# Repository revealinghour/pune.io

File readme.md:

https://www.sparkfun.com/tutorials/393
https://www.kickstarter.com/projects/acrobotic/the-smart-citizen-kit-crowdsourced-environmental-m

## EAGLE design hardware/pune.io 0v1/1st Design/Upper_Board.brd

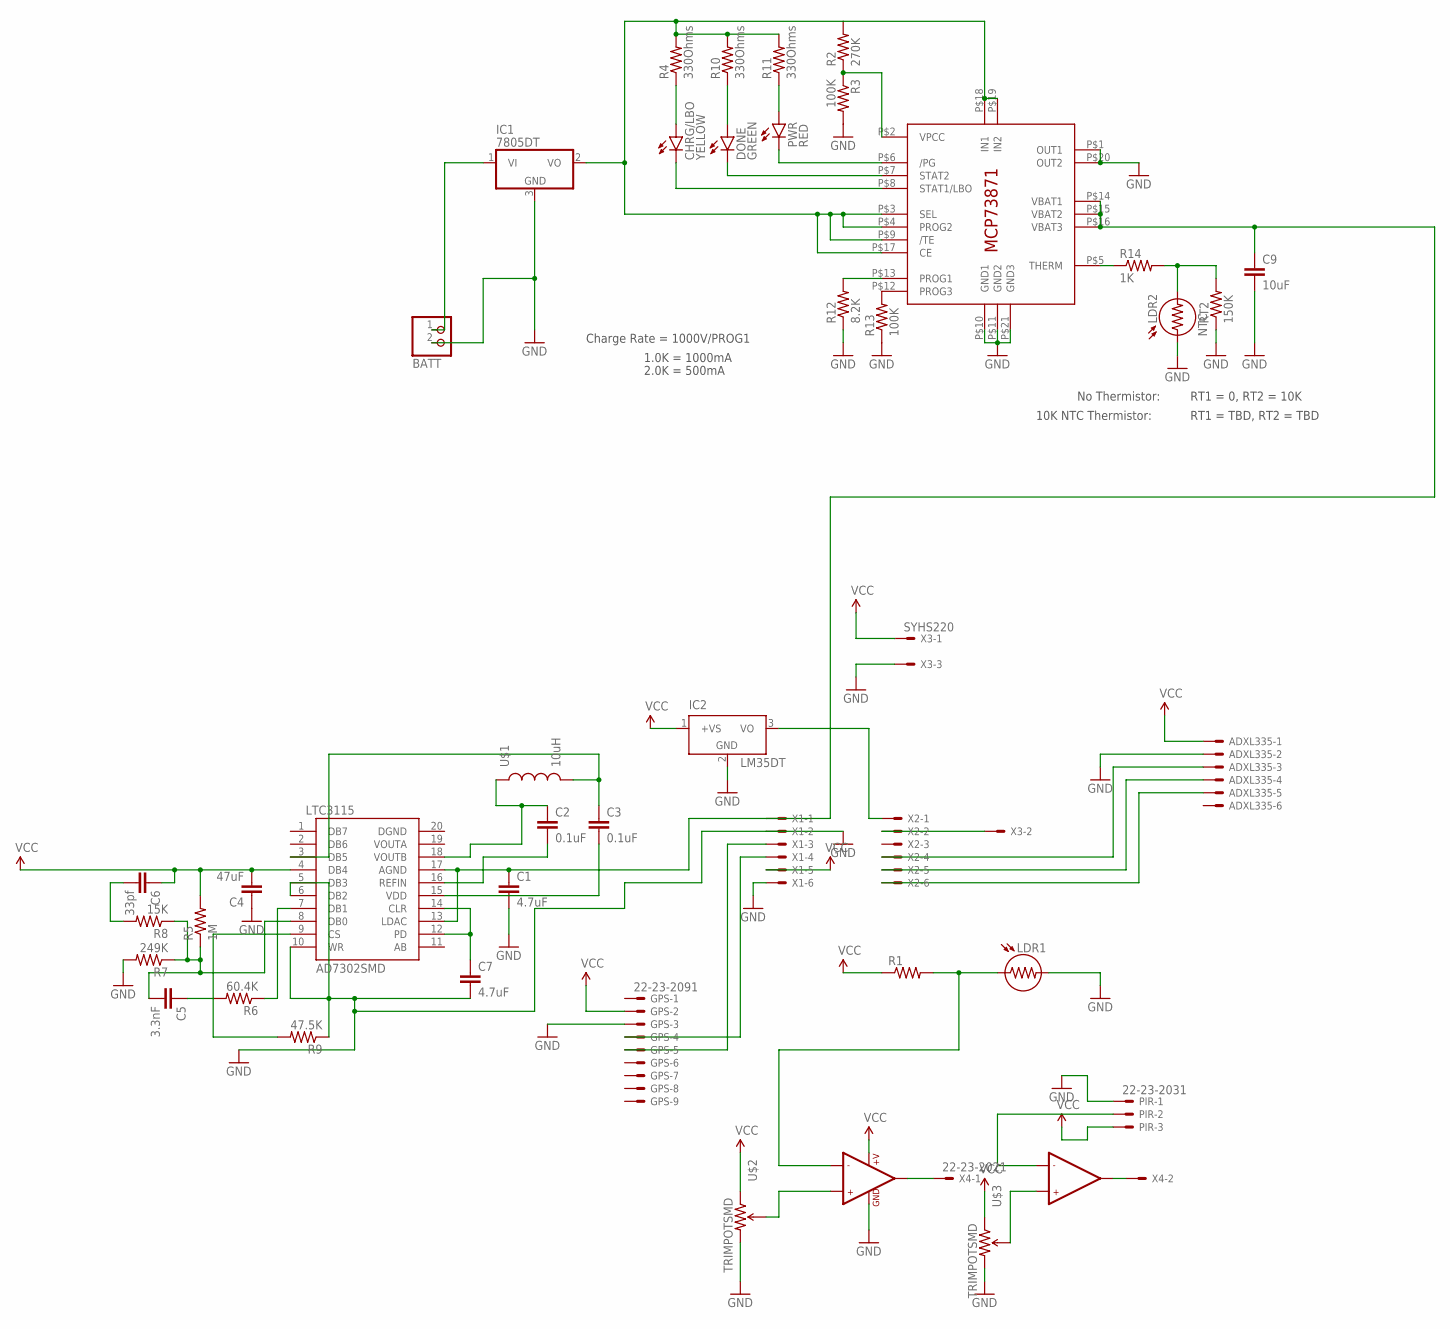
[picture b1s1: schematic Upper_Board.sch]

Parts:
ADXL335: 22-23-2061
BATT: JST_2PIN-SMT-RA; JST-PH-2-SMT-RA
C1, C7: 4.7uF; 0603-CAP
C2, C3: 0.1uF; 0603-CAP
C4: 47uF; 0603-CAP
C5: 3.3nF; 0603-CAP
C6: 33pf; 0603-CAP
C9: 10uF; 0603-CAP
CHRG/LBO: YELLOW; LED-1206
DONE: GREEN; LED-1206
GPS: 22-23-2091
IC1: 7805DT; TO252
IC2: LM35DT; TO220V
IC4: MCP73871; QFN20_4MM
LDR1: LDR5MM; LDR338-54C
LDR2: NTC; LDR338-54C
LTC3115: AD7302SMD; TSSOP20
PIR: 22-23-2031
PWR: RED; LED-1206
R1: RESISTOR1206; 1206
R2: 270K; 1206
R3, R13: 100K; 1206
R4, R10, R11: 330Ohms; 1206
R5: 1M; 1206
R6: 60.4K; 1206
R7: 249K; 1206
R8: 15K; 1206
R9: 47.5K; 1206
R12: 8.2K; 1206
R14: 1K; 1206
RT2: 150K; 1206
U$1: 10uH; INDUCTOR-1206
U$2, U$3: TRIMPOTSMD; TRIMPOT-3MM
U$4: LMV358; SO08
X1, X2: 22-23-2061
X3: SYHS220; 22-23-2031
X4: 22-23-2021

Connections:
BATT: C1.1, C9.1, IC4.P$14 (VBAT1), IC4.P$15 (VBAT2), IC4.P$16 (VBAT3), LTC3115.13 (LDAC), LTC3115.17 (AGND), X1.1
GND: ADXL335.2, BATT.2 (1), C1.2, C4.1, C7.2, C9.2, GPS.3, IC1.3 (GND), IC2.2 (GND), IC4.P$1 (OUT1), IC4.P$10 (GND1), IC4.P$11 (GND2), IC4.P$20 (OUT2), IC4.P$21 (GND3), LDR1.2, LDR2.1, LTC3115.5 (DB3), LTC3115.6 (DB2), LTC3115.10 (WR), PIR.1, R3.2, R7.2, R9.1, R12.1, R13.1, RT2.1, U$2.3 (CW), U$3.3 (CW), U$4.4 (GND), X1.2, X1.6, X3.3
unnamed: LDR1.1, R1.2, U$4.2 (-IN1)
unnamed: IC2.3 (VO), X2.1
unnamed: U$4.1 (OUT1), X4.1
unnamed: U$4.7 (OUT2), X4.2
unnamed: U$2.2 (WIPER), U$4.3 (+IN1)
unnamed: U$3.2 (WIPER), U$4.5 (+IN2)
unnamed: X2.2, X3.2
unnamed: IC4.P$2 (VPCC), R2.1, R3.1
unnamed: ADXL335.3, X2.4
unnamed: PIR.2, U$4.6 (-IN2)
unnamed: ADXL335.4, X2.5
unnamed: ADXL335.5, X2.6
unnamed: IC4.P$6 (/PG), PWR.C
unnamed: DONE.C, IC4.P$7 (STAT2)
unnamed: CHRG/LBO.C, IC4.P$8 (STAT1/LBO)
unnamed: C2.2, LTC3115.16 (REFIN)
unnamed: C2.1, LTC3115.18 (VOUTB), U$1.P$1 (1)
unnamed: C3.1, LTC3115.3 (DB5), U$1.P$2 (2)
unnamed: C3.2, LTC3115.15 (VDD)
unnamed: CHRG/LBO.A, R4.1
unnamed: LTC3115.7 (DB1), R6.1
unnamed: C5.1, R6.2
unnamed: C5.2, LTC3115.8 (DB0), R5.1, R7.1, R8.1
unnamed: DONE.A, R10.1
unnamed: C6.2, R8.2
unnamed: PWR.A, R11.1
unnamed: C7.1, LTC3115.12 (PD), LTC3115.14 (CLR)
unnamed: IC4.P$12 (PROG3), R13.2
unnamed: IC4.P$13 (PROG1), R12.2
unnamed: LTC3115.9 (CS), R9.2
unnamed: IC4.P$5 (THERM), R14.1
unnamed: LDR2.2, R14.2, RT2.2
unnamed: IC1.2 (VO), IC4.P$3 (SEL), IC4.P$4 (PROG2), IC4.P$9 (/TE), IC4.P$17 (CE), IC4.P$18 (IN1), IC4.P$19 (IN2), R2.2, R4.2, R10.2, R11.2
unnamed: GPS.4, X1.4
unnamed: GPS.5, X1.3
unnamed: BATT.1 (2), IC1.1 (VI)
VCC: ADXL335.1, C4.2, C6.1, GPS.2, IC2.1 (+VS), LTC3115.4 (DB4), PIR.3, R1.1, R5.2, U$2.1 (CCW), U$3.1 (CCW), U$4.8 (+V), X1.5, X3.1

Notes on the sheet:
Charge Rate = 1000V/PROG1
1.0K = 1000mA
2.0K = 500mA
No Thermistor:
10K NTC Thermistor:
RT1 = 0, RT2 = 10K
RT1 = TBD, RT2 = TBD

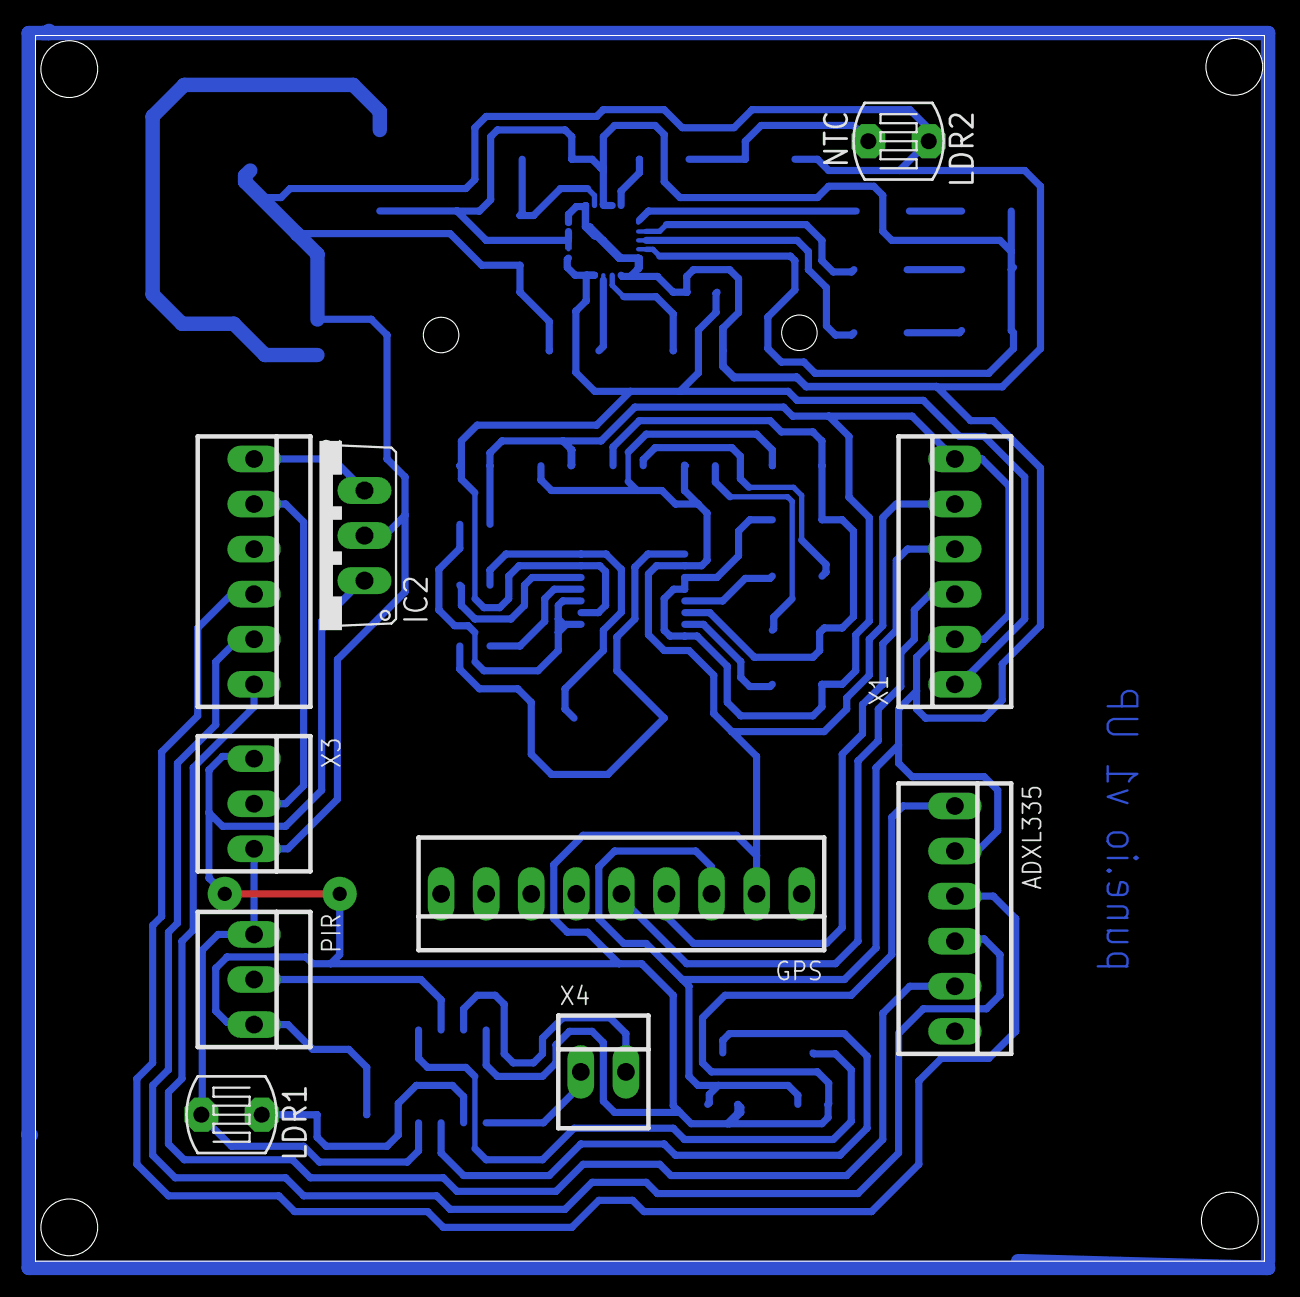
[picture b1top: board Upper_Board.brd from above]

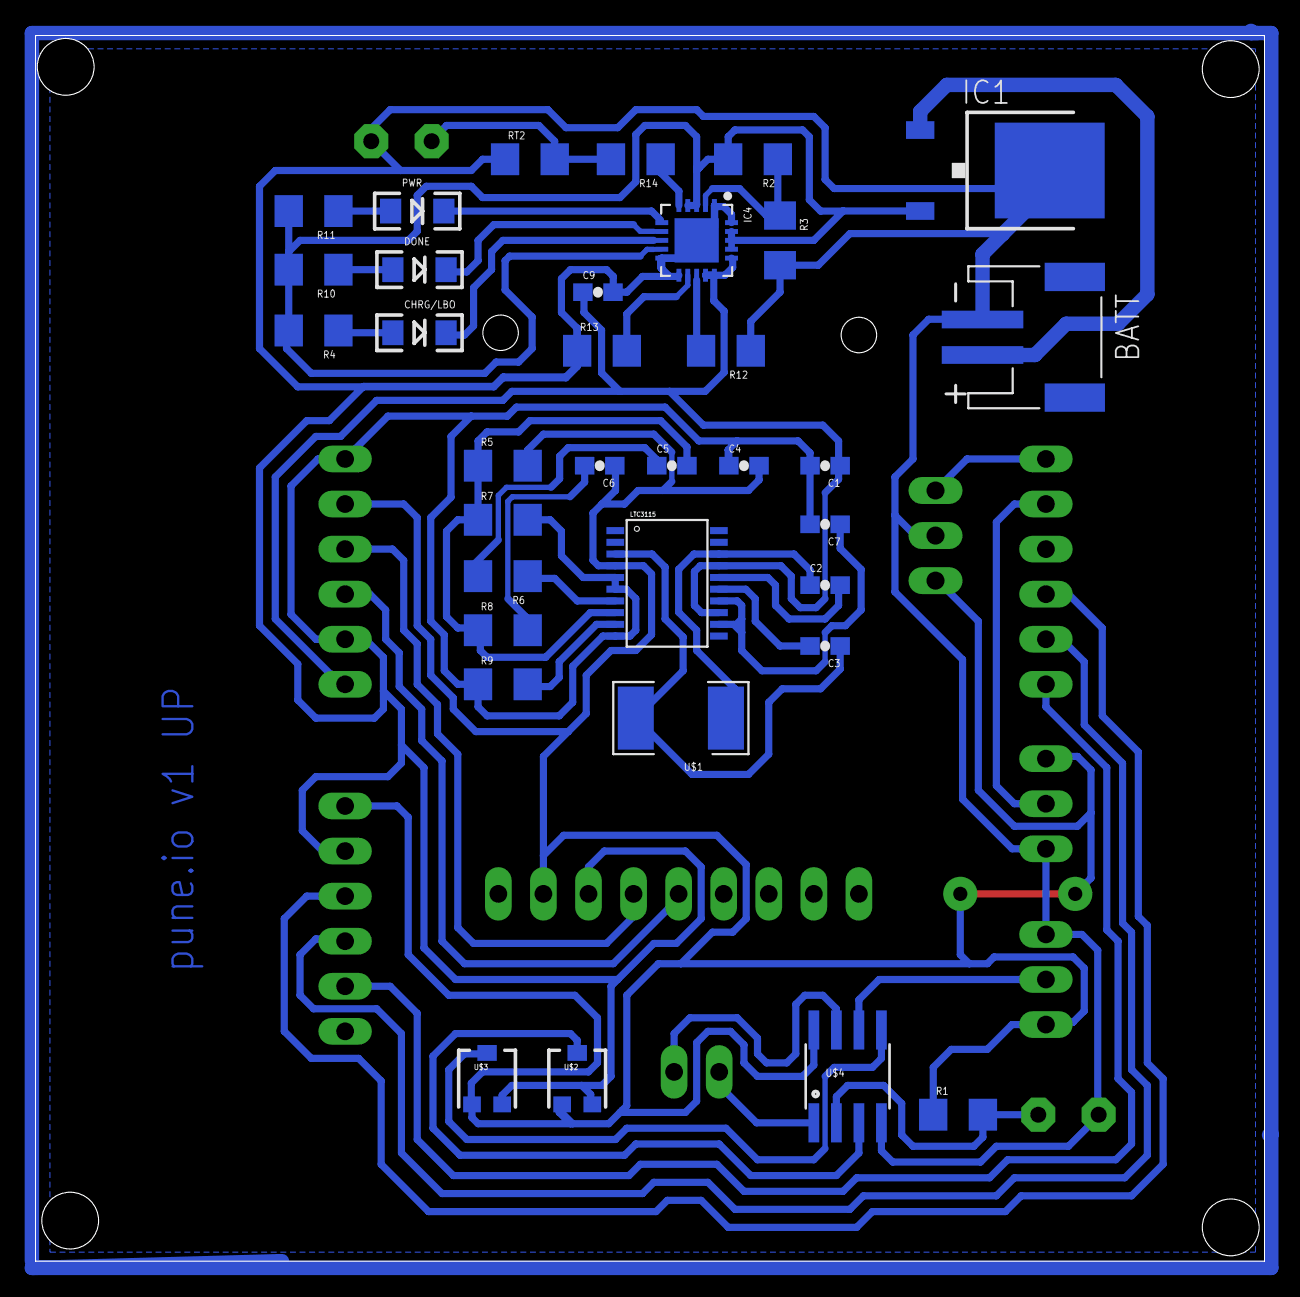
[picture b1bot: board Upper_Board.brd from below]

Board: 2 copper layers, 69.3 x 69.1 mm, 44 parts (34 on the bottom side), 39 nets.

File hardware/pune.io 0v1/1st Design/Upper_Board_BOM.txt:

Partlist exported from /home/tanmayee/eagle/Rev/Upper_Board.sch at 20/02/15 6:37 PM

Part     Value      Device          Package         Description                                 MF    MPN        OC_FARNELL OC_NEWARK PROD_ID   VALUE 
ADXL335             22-23-2061      22-23-2061      .100" (2.54mm) Center Header - 6 Pin        MOLEX 22-23-2061 1462922    27C1933                   
BATT                JST_2PIN-SMT-RA JST-PH-2-SMT-RA JST 2-Pin Connectors of various flavors                                                           
C1       4.7uF      CAP0603-CAP     0603-CAP        Capacitor                                                                                         
C2       0.1uF      CAP0603-CAP     0603-CAP        Capacitor                                                                                         
C3       0.1uF      CAP0603-CAP     0603-CAP        Capacitor                                                                                         
C4       47uF       CAP0603-CAP     0603-CAP        Capacitor                                                                                         
C5       3.3nF      CAP0603-CAP     0603-CAP        Capacitor                                                                                         
C6       33pf       CAP0603-CAP     0603-CAP        Capacitor                                                                                         
C7       4.7uF      CAP0603-CAP     0603-CAP        Capacitor                                                                                         
C9       10uF       CAP0603-CAP     0603-CAP        Capacitor                                                                                         
CHRG/LBO YELLOW     LED-YELLOWLARGE LED-1206        Yellow SMD LEDs                                                                   DIO-00820 YELLOW
DONE     GREEN      LED-GREENLARGE  LED-1206        Various green LEDs                                                                DIO-00862 GREEN 
GPS      22-23-2091 22-23-2091      22-23-2091      .100" (2.54mm) Center Header - 9 Pin        MOLEX 22-23-2091 1756827    56H0450                   
IC1      7805DT     7805DT          TO252           Positive VOLTAGE REGULATOR                                                                        
IC2      LM35DT     LM35DT          TO220V          Single-Supply Centigrade Temperature Sensor                                                       
IC4      MCP73871   MCP73871        QFN20_4MM                                                                                                         
LDR1                LDR5MM          LDR338-54C                                                                                                        
LDR2     NTC        LDR5MM          LDR338-54C                                                                                                        
LTC3115  AD7302SMD  AD7302SMD       TSSOP20         8-bit parallel input 2-output DAC                                                                 
PIR      22-23-2031 22-23-2031      22-23-2031      .100" (2.54mm) Center Header - 3 Pin        MOLEX 22-23-2031 1462950    30C0862                   
PWR      RED        LED-RED1206     LED-1206        Assorted Red LEDs                                                                 DIO-00809 RED   
R1                  RESISTOR1206    1206            Resistor                                                                                          
R2       270K       RESISTOR1206    1206            Resistor                                                                                          
R3       100K       RESISTOR1206    1206            Resistor                                                                                          
R4       330Ohms    RESISTOR1206    1206            Resistor                                                                                          
R5       1M         RESISTOR1206    1206            Resistor                                                                                          
R6       60.4K      RESISTOR1206    1206            Resistor                                                                                          
R7       249K       RESISTOR1206    1206            Resistor                                                                                          
R8       15K        RESISTOR1206    1206            Resistor                                                                                          
R9       47.5K      RESISTOR1206    1206            Resistor                                                                                          
R10      330Ohms    RESISTOR1206    1206            Resistor                                                                                          
R11      330Ohms    RESISTOR1206    1206            Resistor                                                                                          
R12      8.2K       RESISTOR1206    1206            Resistor                                                                                          
R13      100K       RESISTOR1206    1206            Resistor                                                                                          
R14      1K         RESISTOR1206    1206            Resistor                                                                                          
RT2      150K       RESISTOR1206    1206            Resistor                                                                                          
U$1      10uH       INDUCTOR1206H*  INDUCTOR-1206   Inductors                                                                                         
U$2      TRIMPOTSMD TRIMPOTSMD      TRIMPOT-3MM                                                                                                       
U$3      TRIMPOTSMD TRIMPOTSMD      TRIMPOT-3MM                                                                                                       
U$4      LMV358     LMV358          SO08                                                                                                              
X1                  22-23-2061      22-23-2061      .100" (2.54mm) Center Header - 6 Pin        MOLEX 22-23-2061 1462922    27C1933                   
X2                  22-23-2061      22-23-2061      .100" (2.54mm) Center Header - 6 Pin        MOLEX 22-23-2061 1462922    27C1933                   
X3       SYHS220    22-23-2031      22-23-2031      .100" (2.54mm) Center Header - 3 Pin        MOLEX 22-23-2031 1462950    30C0862                   
X4       22-23-2021 22-23-2021      22-23-2021      .100" (2.54mm) Center Header - 2 Pin        MOLEX 22-23-2021 1462926    25C3832

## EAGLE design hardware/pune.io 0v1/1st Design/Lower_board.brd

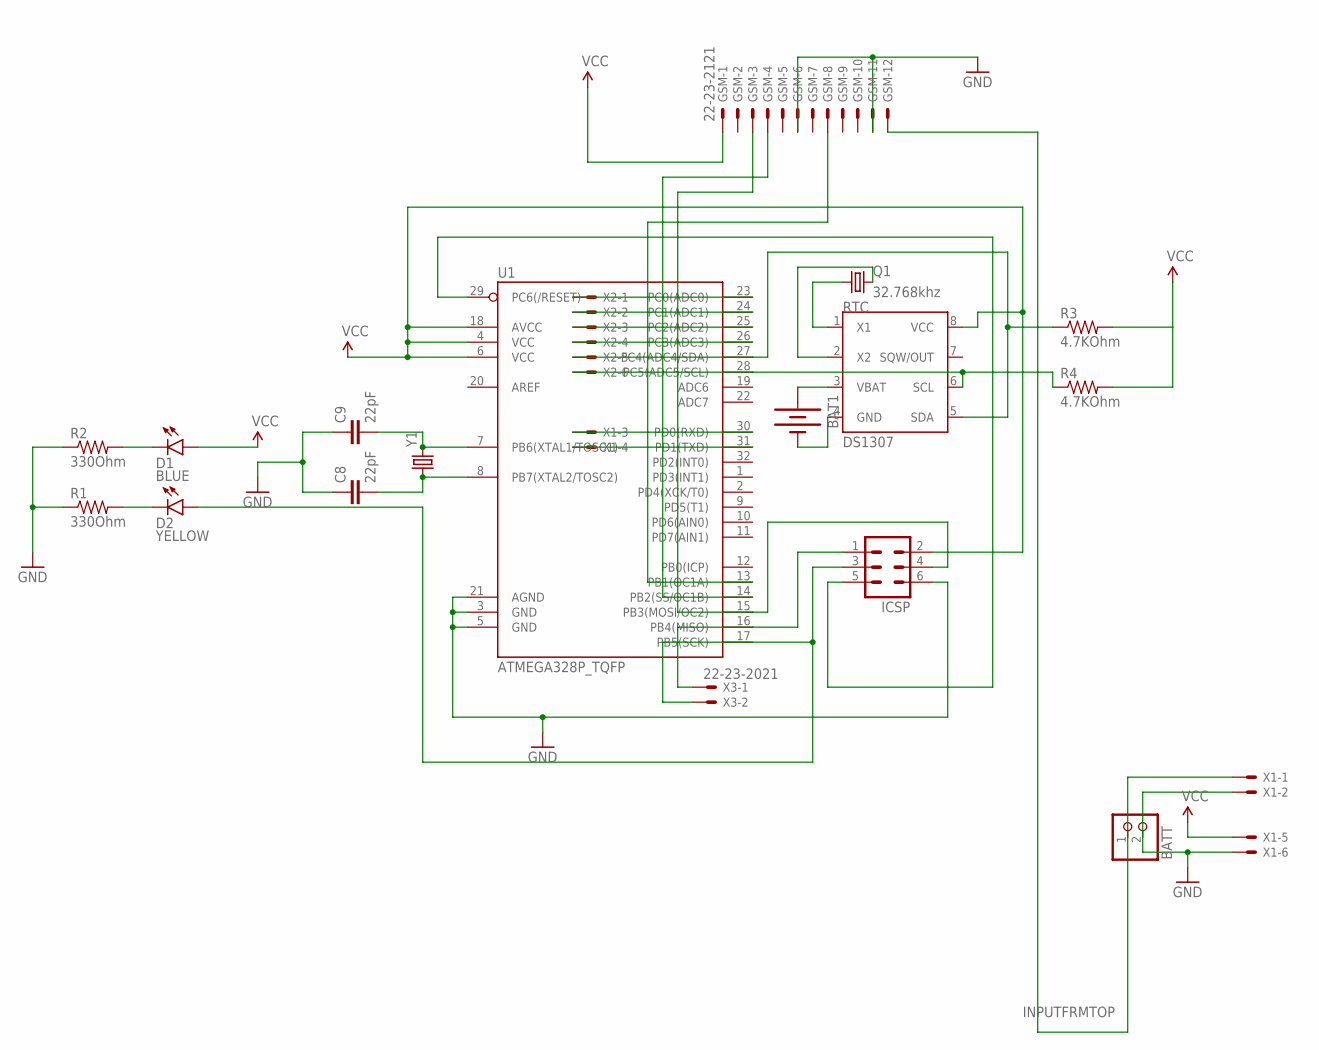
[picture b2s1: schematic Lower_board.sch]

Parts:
BAT1: BATTERY20PTH; BATTCOM_20MM_PTH
BATT: JST_2PIN-SMT-RA; JST-PH-2-SMT-RA
C8, C9: 22pF; 0603-CAP
D1: BLUE; LED-1206
D2: YELLOW; LED-1206
GSM: 22-23-2121
ICSP: ML6
Q1: 32.768khz; CRYSTAL-TXC-7A
R1, R2: 330Ohm; 1206
R3, R4: 4.7KOhm; 1206
RTC: DS1307; SOIC-8
U1: ATMEGA328P_TQFP; TQFP32-08
X1, X2: 22-23-2061
X3: 22-23-2021
Y1: CRYSTALTXC-7A; CRYSTAL-TXC-7A

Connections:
GND: BATT.2 (1), C8.1, C9.1, GSM.6, GSM.11, ICSP.6, R1.1, R2.1, U1.3 (GND), U1.5 (GND), U1.21 (AGND), X1.2, X1.6
INPUTFRMTOP: BATT.1 (2), GSM.12, X1.1
unnamed: BAT1.1 (+), RTC.3 (VBAT)
unnamed: BAT1.2 (-), RTC.4 (GND)
unnamed: Q1.P$1 (1), RTC.1 (X1)
unnamed: ICSP.1, U1.16 (PB4(MISO)), X3.1
unnamed: ICSP.5, U1.29 (PC6(/RESET))
unnamed: D2.A, ICSP.3, X3.2
unnamed: Q1.P$2 (2), RTC.2 (X2)
unnamed: R4.1, RTC.6 (SCL), U1.28 (PC5(ADC5/SCL)), X2.6
unnamed: GSM.4, U1.14 (PB2(SS/OC1B))
unnamed: GSM.3, ICSP.4, U1.15 (PB3(MOSI/OC2))
unnamed: D1.C, R2.2
unnamed: D2.C, R1.2
unnamed: GSM.8, U1.13 (PB1(OC1A))
unnamed: R3.1, RTC.5 (SDA), U1.27 (PC4(ADC4/SDA)), X2.5
unnamed: U1.23 (PC0(ADC0)), X2.1
unnamed: U1.24 (PC1(ADC1)), X2.2
unnamed: U1.25 (PC2(ADC2)), X2.3
unnamed: U1.26 (PC3(ADC3)), X2.4
unnamed: U1.30 (PD0(RXD)), X1.3
unnamed: U1.31 (PD1(TXD)), X1.4
unnamed: C9.2, U1.7 (PB6(XTAL1/TOSC1)), Y1.P$2 (2)
unnamed: C8.2, U1.8 (PB7(XTAL2/TOSC2)), Y1.P$1 (1)
VCC: D1.A, GSM.1, ICSP.2, R3.2, R4.2, RTC.8 (VCC), U1.4 (VCC), U1.6 (VCC), U1.18 (AVCC), X1.5

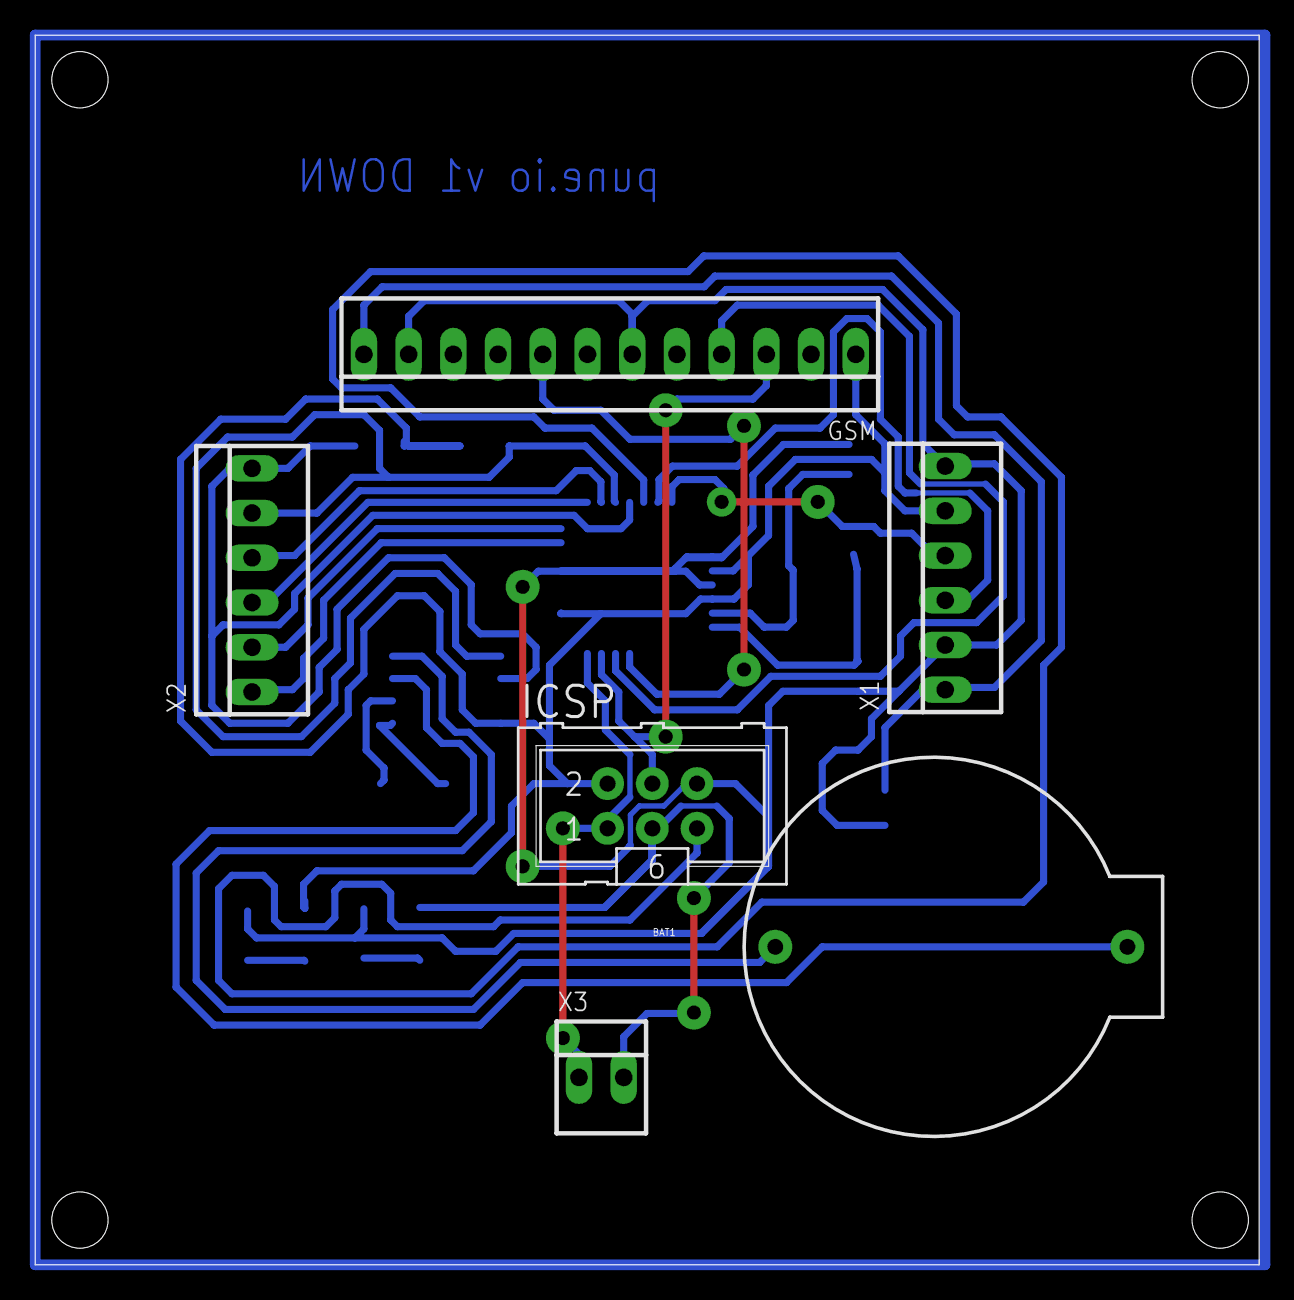
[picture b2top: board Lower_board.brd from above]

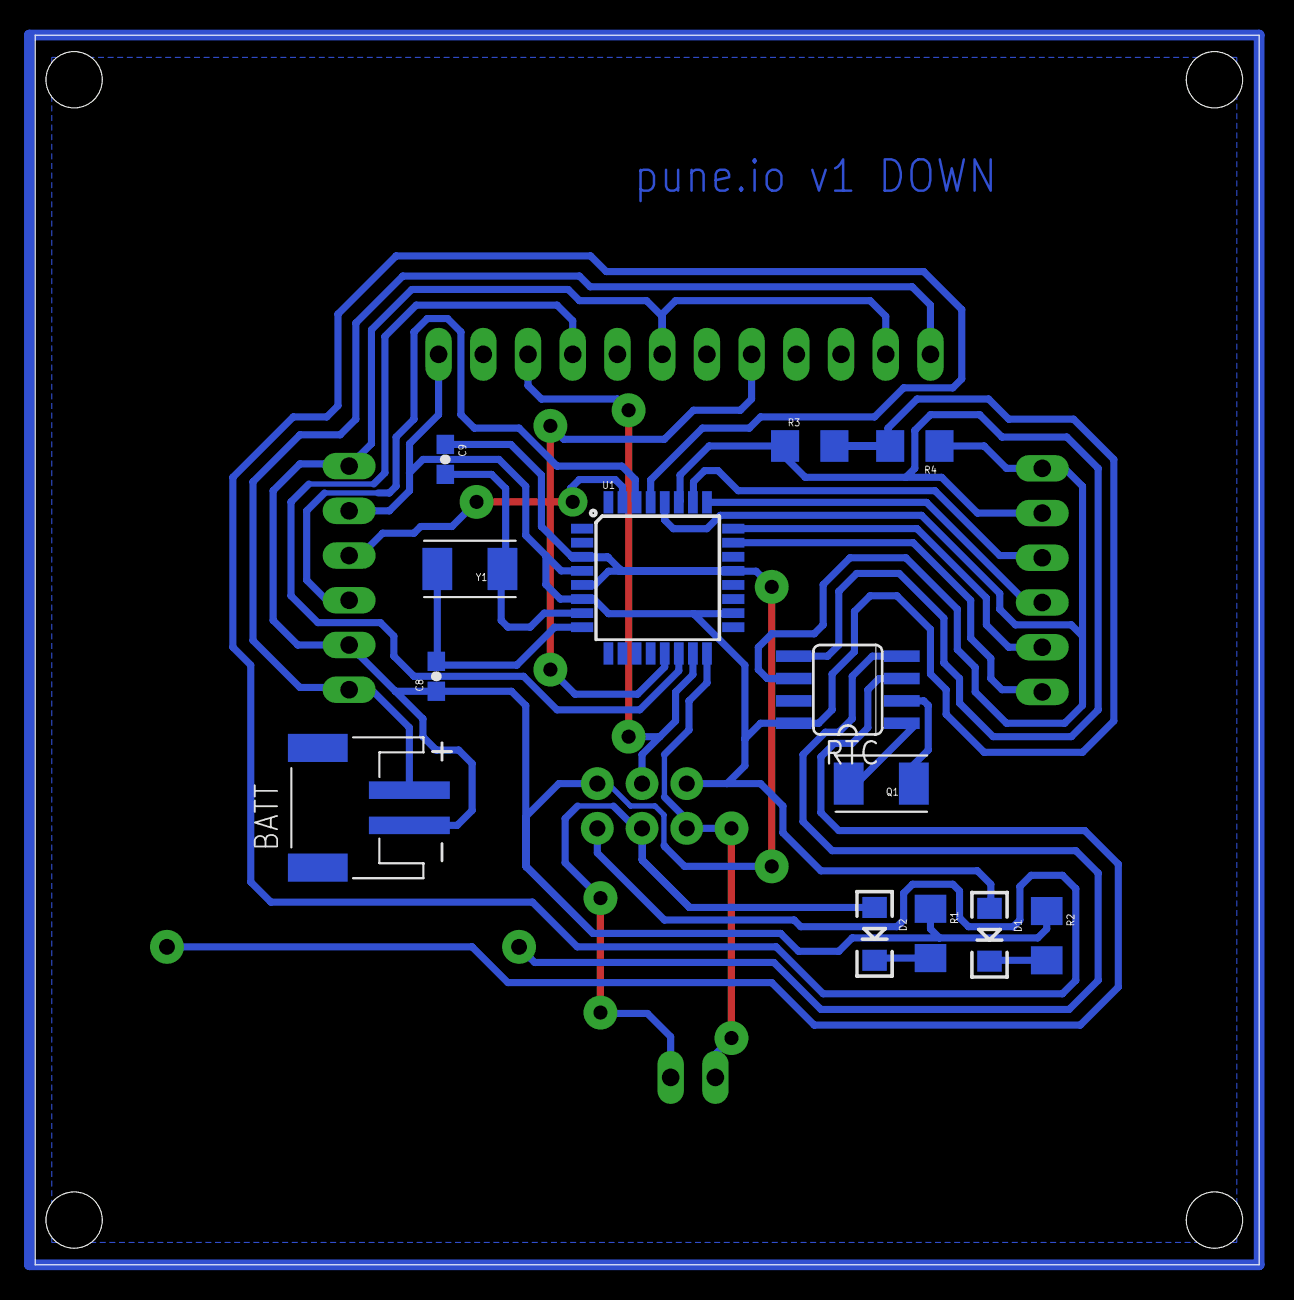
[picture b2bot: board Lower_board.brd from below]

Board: 2 copper layers, 69.5 x 69.8 mm, 19 parts (13 on the bottom side), 25 nets.

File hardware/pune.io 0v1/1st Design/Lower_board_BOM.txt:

Partlist exported from /home/tanmayee/eagle/Rev/Lower_board.sch at 20/02/15 6:35 PM

Part Value           Device          Package          Description                                   MF    MPN        OC_FARNELL OC_NEWARK PROD_ID   VALUE          
BAT1                 BATTERY20PTH    BATTCOM_20MM_PTH Battery Holders                                                                                              
BATT                 JST_2PIN-SMT-RA JST-PH-2-SMT-RA  JST 2-Pin Connectors of various flavors                                                                      
C8   22pF            CAP0603-CAP     0603-CAP         Capacitor                                                                                                    
C9   22pF            CAP0603-CAP     0603-CAP         Capacitor                                                                                                    
D1   BLUE            LED-BLUE1206    LED-1206         Blue LEDs for production use                                                        DIO-09911 BLUE           
D2   YELLOW          LED-YELLOWLARGE LED-1206         Yellow SMD LEDs                                                                     DIO-00820 YELLOW         
GSM  22-23-2121      22-23-2121      22-23-2121       .100" (2.54mm) Center Header - 12 Pin         MOLEX 22-23-2121 1462935    56H0456                            
ICSP                 ML6             ML6              HARTING                                                        unknown    unknown                            
Q1   32.768khz       CRYSTALTXC-7A   CRYSTAL-TXC-7A   Various standard crystals. Proven footprints.                                                                
R1   330Ohm          RESISTOR1206    1206             Resistor                                                                                                     
R2   330Ohm          RESISTOR1206    1206             Resistor                                                                                                     
R3   4.7KOhm         RESISTOR1206    1206             Resistor                                                                                                     
R4   4.7KOhm         RESISTOR1206    1206             Resistor                                                                                                     
RTC  DS1307          DS1307          SOIC-8           I2C Serial RTC w/56 bytes battery backed RAM                                                                 
U1   ATMEGA328P_TQFP ATMEGA328P_TQFP TQFP32-08                                                                                            IC-09069  ATMEGA328P_TQFP
X1                   22-23-2061      22-23-2061       .100" (2.54mm) Center Header - 6 Pin          MOLEX 22-23-2061 1462922    27C1933                            
X2                   22-23-2061      22-23-2061       .100" (2.54mm) Center Header - 6 Pin          MOLEX 22-23-2061 1462922    27C1933                            
X3   22-23-2021      22-23-2021      22-23-2021       .100" (2.54mm) Center Header - 2 Pin          MOLEX 22-23-2021 1462926    25C3832                            
Y1                   CRYSTALTXC-7A   CRYSTAL-TXC-7A   Various standard crystals. Proven footprints.

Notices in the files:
parts and their libraries:
SparkFun-Capacitors: Licensing: Creative Commons ShareAlike 4.0 International - https://creativecommons.org/licenses/by-sa/4.0
